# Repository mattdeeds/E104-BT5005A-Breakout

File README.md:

# E104-BT5005A-Breakout
A simple breakout board for the E104-BT5005A BLE 5.0 module.
The E104-BT5005A is based on nordics nRF52805 and ships with a BLE to serial port firmware controlled with AT commands but can be reprogrammed with a j-link programmer through the swd pins. It can be found for prices under $3 from china and can be soldered easily with carful solder paste application and a hot plate. 

## Board Pinout

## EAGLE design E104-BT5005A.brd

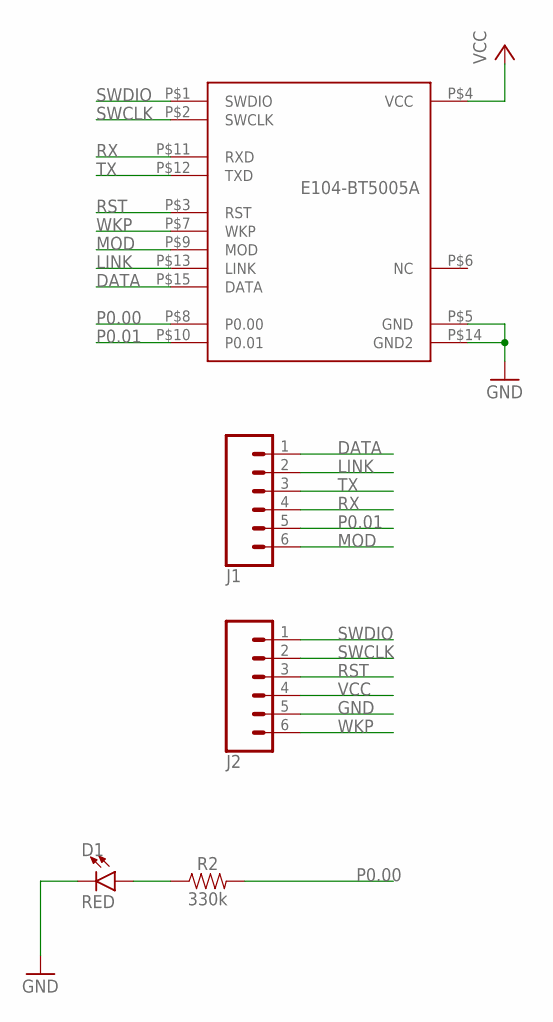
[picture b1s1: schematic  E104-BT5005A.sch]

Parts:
D1: RED; LED-0603
J1, J2: CONN_06SILK_FEMALE_PTH; 1X06
R2: 330k; 0603
U$1: E104-BT5005A

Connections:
DATA: J1.1, U$1.P$15 (DATA)
GND: D1.C, J2.5, U$1.P$5 (GND), U$1.P$14 (GND2)
LINK: J1.2, U$1.P$13 (LINK)
MOD: J1.6, U$1.P$9 (MOD)
unnamed: D1.A, R2.1
P0.00: R2.2, U$1.P$8 (P0.00)
P0.01: J1.5, U$1.P$10 (P0.01)
RST: J2.3, U$1.P$3 (RST)
RX: J1.4, U$1.P$11 (RXD)
SWCLK: J2.2, U$1.P$2 (SWCLK)
SWDIO: J2.1, U$1.P$1 (SWDIO)
TX: J1.3, U$1.P$12 (TXD)
VCC: J2.4, U$1.P$4 (VCC)
WKP: J2.6, U$1.P$7 (WKP)

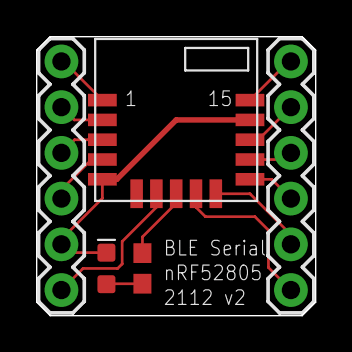
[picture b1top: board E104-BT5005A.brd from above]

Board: 2 copper layers, 15.5 x 15.5 mm, 5 parts (0 on the bottom side), 14 nets.

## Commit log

2021-03-16 added eagle sch and brd files
2021-03-16 Added gerber zip for osh park 2 layer
2021-03-22 v2 fixes, errors with part library
    the original module library had errors. fixed module and silkscreen, added eagle library for ble module

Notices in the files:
parts and their libraries:
SparkFun-Connectors: Licensing: Creative Commons ShareAlike 4.0 International - https://creativecommons.org/licenses/by-sa/4.0
